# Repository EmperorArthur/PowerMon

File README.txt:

This is the code and Eagle files for a wireless power monitoring system.
All code and schematics are Copyright Arthur Moore 2013 GPLV3
	If this license is too restrictive for your use, feel free to contact me.

The wireless power monitor works using two boards with IEE 802.15.4 Radios.
One board monitors and transmits power usage data, while the other recieves the data, and sends it on to a computer.

Currently there is one board that does everything.  It uses an ATMega328 microcontroller with an AT86RF231 radio module.

This repository was taken from an SVN snapshot, then sanitized for public release.

The code is in ./Code/Datalogger1/

Important files are:
ADC.h/c:				These are the Analog to Digital Converter functions.
LED.h/c:				Simple functions to controll a LED
Communication.h/c:		Bridge functions, allowing cout to work with both serial and the radio.
UART.h/c:				Serial I/O for cout and cin
Measurements.h/c:		Where the actual measurements are done and calculated.
Datalogger1.c:			The main file.  This is where the important stuff takes place.

Contrary to any common sense, the main board is in ./Eagle Files/Main Board with Headers/

The only header on the board is a SPI programming header.
I normally use an arduino bootloader with the FTDI chip, so it's mostly unused.
There is one wire missing for this configuration.  A wire from the FTDI chip to the reset pin with a small capacitor in series.

I was orriginally using an older version of the radio library provided here:  http://simonetti.media.mit.edu/dev/projects/avrradio
Given my issues with the library documentation and microcontroller space issues, I had to hack the provided library to pieces.
I eventually ended up creating my own library from scratch for this thing.  See my github page for it.

To Do:
	Replace hacked together radio library with the one I created.
	Re-organize the repository so It's easy to understand, and doesn't have as many misc files.
	Completely redesign board for smaller footprint, less component count, and higher acuracy.
	Potentially seperate board into two seperate boards.

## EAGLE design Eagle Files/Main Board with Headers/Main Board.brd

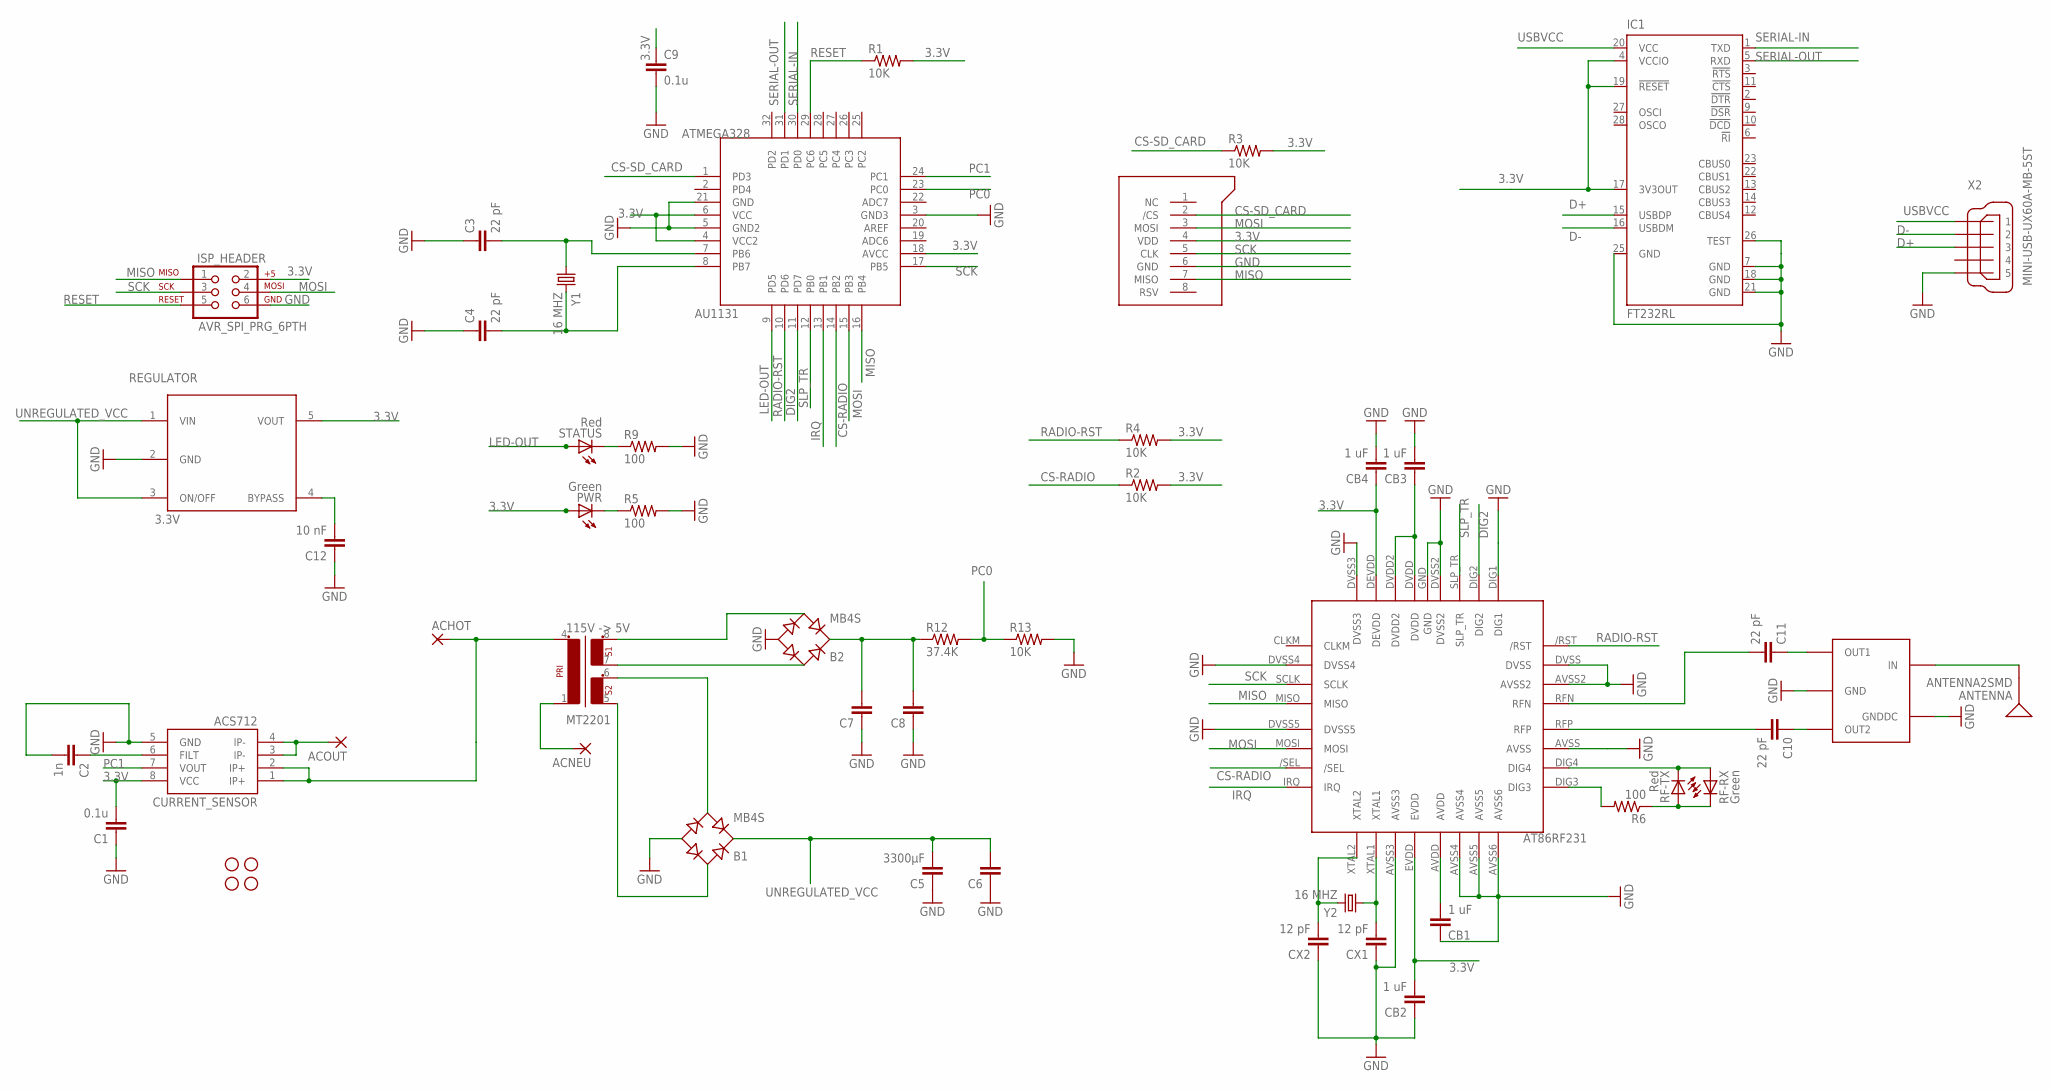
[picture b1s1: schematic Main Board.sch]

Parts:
3.3V_REGULATOR: REG3.3V; SOT23-5
ACHOT: PTH3MM; PTH-3MM
ACNEU: PTH3MM; PTH-3MM
ACOUT: PTH3MM; PTH-3MM
ANTENNA: ANTENNA2SMD; ANTENNA-CHIP2
AT86RF231: AT86RF231(RADIO)AT86RF231; 32QN2(RADIO)
ATMEGA328: ATMEGA32832A; TQFP32-08
B1, B2: MB4S; SOIC-4
BALUN: WE-BAL
C1, C9: 0.1u; 0603-CAP
C2: 1n; 0603-CAP
C3, C4, C10, C11: 22 pF; 0603-CAP
C5: 3300µF; CAP-PTH-5MM
C6, C7, C8: CAPPTH1; CAP-PTH-5MM
C12: 10 nF; 0603-CAP
CB1, CB2, CB3, CB4: 1 uF; 0603-CAP
CURRENT_SENSOR: ACS712; SO08
CX1, CX2: 12 pF; 0603-CAP
IC1: FT232RL; SSOP28
ISP_HEADER: AVR_SPI_PRG_6PTH; 2X3
JP1, JP2, JP3, JP4: STAND-OFF
MICROSD: MICROSD; MICRO-SD-SOCKET-PP
MT2201: 115V -> 5V; EI38-2
PWR: Green; LED-0603
R1, R2, R3, R4, R13: 10K; 0603-RES
R5, R6, R9: 100; 0603-RES
R12: 37.4K; 0603-RES
RF-RX: Green; LED-0603
RF-TX: Red; LED-0603
STATUS: Red; LED-0603
X2: MINI-USB-UX60A-MB-5ST; UX60A-MB-5ST
Y1, Y2: 16 MHZ; HC49UP

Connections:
3.3V: 3.3V_REGULATOR.5 (VOUT), AT86RF231.DEVDD, AT86RF231.EVDD, ATMEGA328.4 (VCC2), ATMEGA328.6 (VCC), ATMEGA328.18 (AVCC), C1.2, C9.1, CB2.2, CB4.1, CURRENT_SENSOR.8 (VCC), IC1.4 (VCCIO), IC1.17 (3V3OUT), IC1.19 (!RESET), ISP_HEADER.2, MICROSD.4 (VDD), PWR.A, R1.2, R2.2, R3.2, R4.2
3.3V1: 3.3V_REGULATOR.4 (BYPASS), C12.2
CS-RADIO: AT86RF231./SEL, ATMEGA328.14 (PB2), R2.1
CS-SD_CARD: ATMEGA328.1 (PD3), MICROSD.2 (/CS), R3.1
D+: IC1.15 (USBDP), X2.3
D-: IC1.16 (USBDM), X2.2
DIG2: AT86RF231.DIG2, ATMEGA328.11 (PD7)
GND: 3.3V_REGULATOR.2 (GND), AT86RF231.AVSS, AT86RF231.AVSS2, AT86RF231.AVSS3, AT86RF231.AVSS4, AT86RF231.AVSS5, AT86RF231.AVSS6, AT86RF231.DIG1, AT86RF231.DVSS, AT86RF231.DVSS2, AT86RF231.DVSS3, AT86RF231.DVSS4, AT86RF231.DVSS5, AT86RF231.GND, ATMEGA328.3 (GND3), ATMEGA328.5 (GND2), ATMEGA328.21 (GND), B1.-, B2.-, BALUN.GND, BALUN.GNDDC, C1.1, C2.2, C3.1, C4.1, C5.1, C6.1, C7.1, C8.1, C9.2, C12.1, CB1.1, CB2.1, CB3.2, CB4.2, CURRENT_SENSOR.5 (GND), CX1.1, CX2.1, IC1.7 (GND), IC1.18 (GND), IC1.21 (GND), IC1.25 (GND), IC1.26 (TEST), ISP_HEADER.6, MICROSD.6 (GND), R5.2, R9.2, R13.2, X2.5
IRQ: AT86RF231.IRQ, ATMEGA328.13 (PB1)
LED-OUT: ATMEGA328.9 (PD5), STATUS.A
MISO: AT86RF231.MISO, ATMEGA328.16 (PB4), ISP_HEADER.1, MICROSD.7 (MISO)
MOSI: AT86RF231.MOSI, ATMEGA328.15 (PB3), ISP_HEADER.4, MICROSD.3 (MOSI)
unnamed: ACHOT.1, CURRENT_SENSOR.1 (IP+), CURRENT_SENSOR.2 (IP+), MT2201.4
unnamed: ACNEU.1, MT2201.1
unnamed: B1.~1 (AC1), MT2201.5
unnamed: B2.~1 (AC1), MT2201.7
unnamed: B2.~2 (AC2), MT2201.8
unnamed: B2.+, C7.2, C8.2, R12.1
unnamed: PWR.C, R5.1
unnamed: AT86RF231.DVDD, AT86RF231.DVDD2, CB3.1
unnamed: ACOUT.1, CURRENT_SENSOR.3 (IP-), CURRENT_SENSOR.4 (IP-)
unnamed: AT86RF231.AVDD, CB1.2
unnamed: AT86RF231.XTAL1, CX1.2, Y2.1
unnamed: AT86RF231.XTAL2, CX2.2, Y2.2
unnamed: AT86RF231.DIG4, RF-RX.A, RF-TX.C
unnamed: R6.1, RF-RX.C, RF-TX.A
unnamed: AT86RF231.DIG3, R6.2
unnamed: BALUN.OUT2, C10.1
unnamed: BALUN.OUT1, C11.1
unnamed: AT86RF231.RFN, C11.2
unnamed: AT86RF231.RFP, C10.2
unnamed: ANTENNA.FEED, BALUN.IN
unnamed: B1.~2 (AC2), MT2201.6
unnamed: C2.1, CURRENT_SENSOR.6 (FILT)
unnamed: R9.1, STATUS.C
PC0: ATMEGA328.23 (PC0), R12.2, R13.1
PC1: ATMEGA328.24 (PC1), CURRENT_SENSOR.7 (VOUT)
RADIO-RST: AT86RF231./RST, ATMEGA328.10 (PD6), R4.1
RESET: ATMEGA328.29 (PC6), ISP_HEADER.5, R1.1
SCK: AT86RF231.SCLK, ATMEGA328.17 (PB5), ISP_HEADER.3, MICROSD.5 (CLK)
SERIAL-IN: ATMEGA328.30 (PD0), IC1.1 (TXD)
SERIAL-OUT: ATMEGA328.31 (PD1), IC1.5 (RXD)
SLP_TR: AT86RF231.SLP_TR, ATMEGA328.12 (PB0)
UNREGULATED_VCC: 3.3V_REGULATOR.1 (VIN), 3.3V_REGULATOR.3 (ON/OFF), B1.+, C5.2, C6.2
USBVCC: IC1.20 (VCC), X2.1
XTAL1: ATMEGA328.7 (PB6), C3.2, Y1.1
XTAL2: ATMEGA328.8 (PB7), C4.2, Y1.2

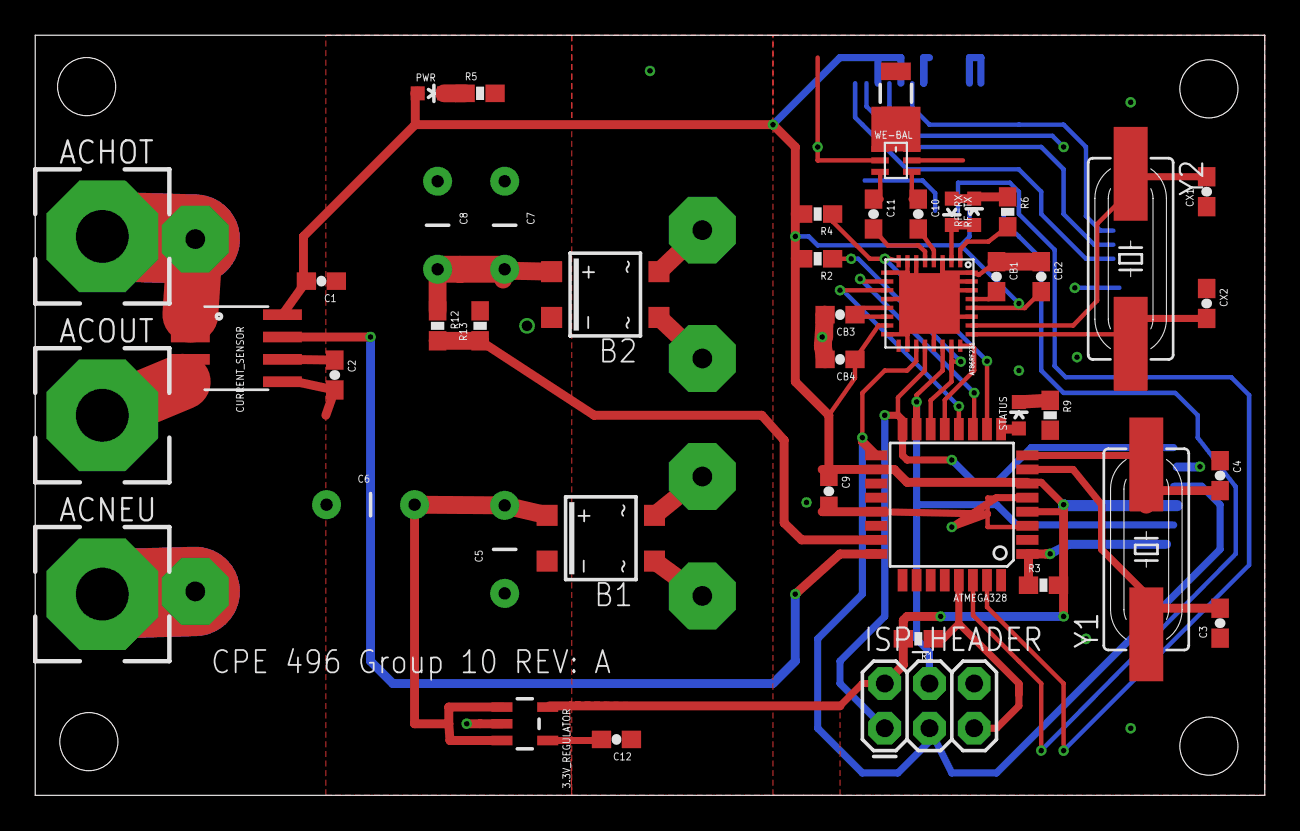
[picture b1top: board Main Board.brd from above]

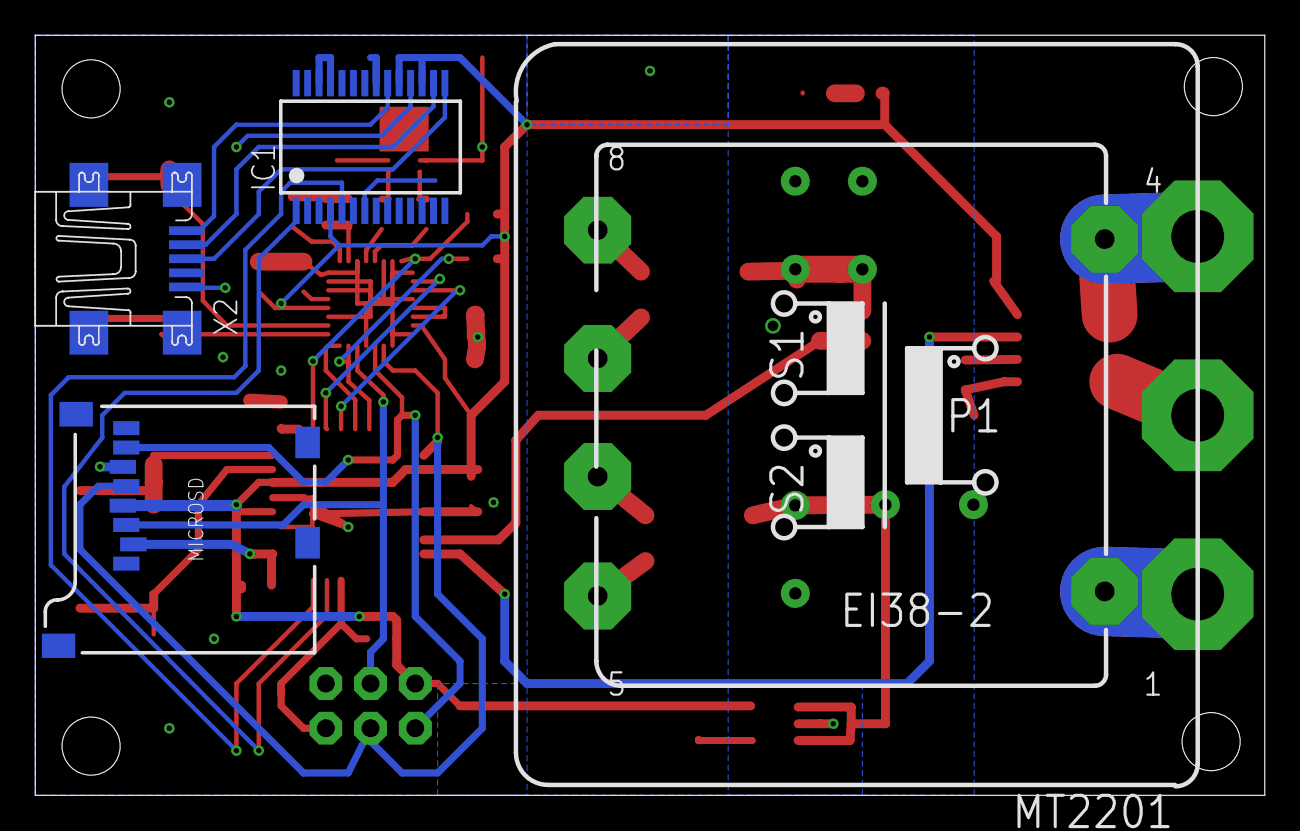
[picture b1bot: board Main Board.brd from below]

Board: 2 copper layers, 69.8 x 43.2 mm, 53 parts (4 on the bottom side), 47 nets.

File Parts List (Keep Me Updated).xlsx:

Qty | Value | Device | Parts | Price Per Part | Price Per Board | For 3 Boards | Part Order Page | Part Description | Already have | Minimum Order
1 | ACS712 | ACS712 | CURRENT_SENSOR | 4.5199999999999996 | 4.5199999999999996 | 13.559999999999999 | http://parts.digikey.com/1/parts/945626-sensor-current-20a-5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 | current-sensor | yes | 3
1 | ANTENNA2SMD | ANTENNA2SMD | ANTENNA | 0.84399999999999997 | 0.84399999999999997 | 2.532 | http://search.digikey.com/us/en/products/2450AT18B100E/712-1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 | RF antenna | no | Order at least 10
1 | AT86RF231(RADIO)AT86RF231 | AT86RF231(RADIO)AT86RF231 | AT86RF231 | 4.7300000000000004 | 4.7300000000000004 | 14.190000000000001 | http://search.digikey.com/us/en/products/AT86RF231-ZU/AT86RF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 | radio | no | 3
1 | ATMEGA32832A | ATMEGA32832A | ATMEGA328 | 3.83 | 3.83 | 11.49 | http://parts.digikey.com/1/parts/1877362-ic-mcu-avr-32k-flas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 | atmega | yes | 3
1 | AVR_SPI_PRG_6PTH | AVR_SPI_PRG_6PTH | ISP_HEADER | 0.39 | 0.78 | 2.34 | http://search.digikey.com/us/en/products/961206-6404-AR/3M94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 | ISP header | no | Order at least 10
2 | 0.1u | CAP0603-CAP | C1, C9 | 1.2500000000000001E-2 | 0.05 | 1.25 | http://search.digikey.com/us/en/products/CC0603ZRY5V9BB104/3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 | 0.1uF Cap | no | Order at least 100
4 | 1 uF | CAP0603-CAP | CB1, CB2, CB3, CB4 | 3.0599999999999999E-2 | 3.0599999999999999E-2 | 3.06 | http://search.digikey.com/us/en/products/C1608Y5V1A105Z/445-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 | 1 uF Caps | no | Order at least 100
1 | 1n | CAP0603-CAP | C2 | 1.5299999999999999E-2 | 1.5299999999999999E-2 | 1.53 | http://search.digikey.com/us/en/products/GRM188R71H102KA01D/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 | 1nF Cap | no | Order at least 100
1 | 10 nF | CAP0603-CAP | C12 | 1.4E-2 | 2.8000000000000001E-2 | 1.4 | http://search.digikey.com/us/en/products/GRM188R71H103KA01D/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 | 10nF Cap | no | Order at least 100
2 | 12 pF | CAP0603-CAP | CX1, CX2 | 2.2499999999999999E-2 | 0.09 | 2.25 | http://search.digikey.com/us/en/products/C1608C0G1H120J/445-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 | 12pF Caps | no | Order at least 100
4 | 22 pF | CAP0603-CAP | C3, C4, C10, C11 | 2.2499999999999999E-2 | 6.7500000000000004E-2 | 2.25 | http://search.digikey.com/us/en/products/C1608C0G1H220J/445-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 | 22pF Caps | no | Order at least 100
3 |  | CAPPTH1 | C6, C7, C8 | - | - | - | - | Ignore these
1 | 3300µF | CAPPTH1 | C5 | 0.9 | 1.8 | 5.4 | http://search.digikey.com/us/en/products/ECA-1CM332/P5144-ND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 | 3300uF Cap | no | 6
2 | 16 MHZ | CRYSTALSMD | Y1, Y2 | 0.35799999999999998 | 0.35799999999999998 | 3.58 | http://parts.digikey.com/1/parts/1800664-crystal-16-000-mhz-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 | 16mhz crystal | yes | Order at least 10
1 | 115V -> 5V | EI38-2 | MT2201 | 4.28 | 4.28 | 12.84 | http://search.digikey.com/us/en/products/3FS-210/MT2201-ND/285599 | transformer | no | 3
1 | FT232RL | FT232RL | IC1 | 4.5 | 9 | 27 | http://parts.digikey.com/1/parts/1501976-ic-usb-fs-serial-ua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 | USB-Serial Chip | no | 6
2 | Green | LED0603 | PWR, RF-RX | 0.11700000000000001 | 0.23400000000000001 | 1.17 | http://search.digikey.com/us/en/products/APT1608SGC/754-1121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 | green led | no | Order at least 10
2 | Red | LED0603 | RF-TX, STATUS | 0.11700000000000001 | 0.23400000000000001 | 1.17 | http://search.digikey.com/us/en/products/APT1608EC/754-1117-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 | red led | no | Order at least 10
2 | MB4S | MB4S | B1, B2 | 0.41399999999999998 | 0.41399999999999998 | 4.1399999999999997 | http://parts.digikey.com/1/parts/1422327-ic-rect-bridge-0-5a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 | bridge rectifier | no | Order at least 10
1 | MICROSD | MICROSD | MICROSD | 1.94 | 1.94 | 5.82 | http://parts.digikey.com/1/parts/1804297-conn-mini-micro-sd-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 | microsd | yes | 3
1 | MINI-USB-UX60A-MB-5ST | MINI-USB-UX60A-MB-5ST | X2 | 1.0229999999999999 | 3.069 | 10.23 | http://search.digikey.com/us/en/products/UX60A-MB-5ST/H2961C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 | mini USB | no | Order at least 10
3 |  | PTH3MM | ACHOT, ACNEU, ACOUT | - | - | - | - | Ignore these
1 | REG3.3V | REG3.3V | 3.3V_REGULATOR | 0.66 | 0.66 | 1.98 | http://parts.digikey.com/1/parts/609150-ic-ldo-reg-3-3v-150m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 | 3.3v regulator | yes | 3
5 | 10K | RESISTOR0603-RES | R1, R2, R3, R4, R13 | 1.5800000000000002E-2 | 7.9000000000000015E-2 | 1.58 | http://search.digikey.com/us/en/products/RNCP0603FTD10K0/RNC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 | 10k resistor | no | Order at least 100
1 | 37.4K | RESISTOR0603-RES | R12 | 1.5800000000000002E-2 | 1.5800000000000002E-2 | 1.58 | http://search.digikey.com/us/en/products/RNCP0603FTD37K4/RNC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 | 37.4K resistor | no | Order at least 100
3 | 100 | RESISTOR0603-RES | R5, R6, R9 | 1.5800000000000002E-2 | 4.7400000000000005E-2 | 1.58 | http://search.digikey.com/us/en/products/RNCP0603FTD100R/RNC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 | 100 ohm resistor | no | Order at least 100
4 | STAND-OFF | STAND-OFF | JP1, JP2, JP3, JP4 | - | - | - | - | Ignore these
1 | WE-BAL | WE-BAL | BALUN | 2.58 | 2.58 | 7.74 | http://parts.digikey.com/1/parts/1790682-balun-ember351-357-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 | balun | no | 3
1 |  |  | To Outlet | 0.79700000000000004 | 0.79700000000000004 | 7.97 | http://search.digikey.com/us/en/products/703W-00%2F07/Q335-N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 | Euro IN |  | Order at least 10
1 |  |  | To Device | 1.1299999999999999 | 1.1299999999999999 | 3.3899999999999997 | http://search.digikey.com/us/en/products/Q-712/Q527-ND/2180784 | Edison Out |  | 3
 |  |  | Wire
1 |  |  | Case | 3 | 3 | 9 | http://search.digikey.com/us/en/products/CU-1874-B/377-1165-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 | Enclosure |  | 3
 |  |  | Board Cost
 |  |  |  |  | 41.62360000000001 | 153.02200000000005 | Total
 |  |  |  |  |  | -28.151200000000017 | Cost overhead from spare/unused parts

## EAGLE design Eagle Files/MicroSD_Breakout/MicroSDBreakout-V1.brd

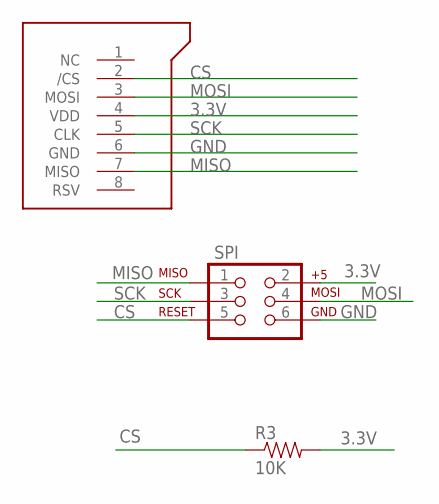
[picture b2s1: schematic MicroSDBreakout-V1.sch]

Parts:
R3: 10K; 0603-RES
SPI: AVR_SPI_PRG_6PTH; 2X3
U$1: MICROSD; MICRO-SD-SOCKET-PP

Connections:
3.3V: R3.2, SPI.2, U$1.4 (VDD)
CS: R3.1, SPI.5, U$1.2 (/CS)
GND: SPI.6, U$1.6 (GND)
MISO: SPI.1, U$1.7 (MISO)
MOSI: SPI.4, U$1.3 (MOSI)
SCK: SPI.3, U$1.5 (CLK)

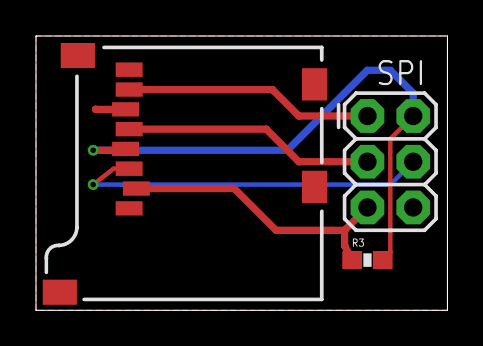
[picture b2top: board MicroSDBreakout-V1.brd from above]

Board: 2 copper layers, 22.9 x 15.2 mm, 3 parts (0 on the bottom side), 6 nets.

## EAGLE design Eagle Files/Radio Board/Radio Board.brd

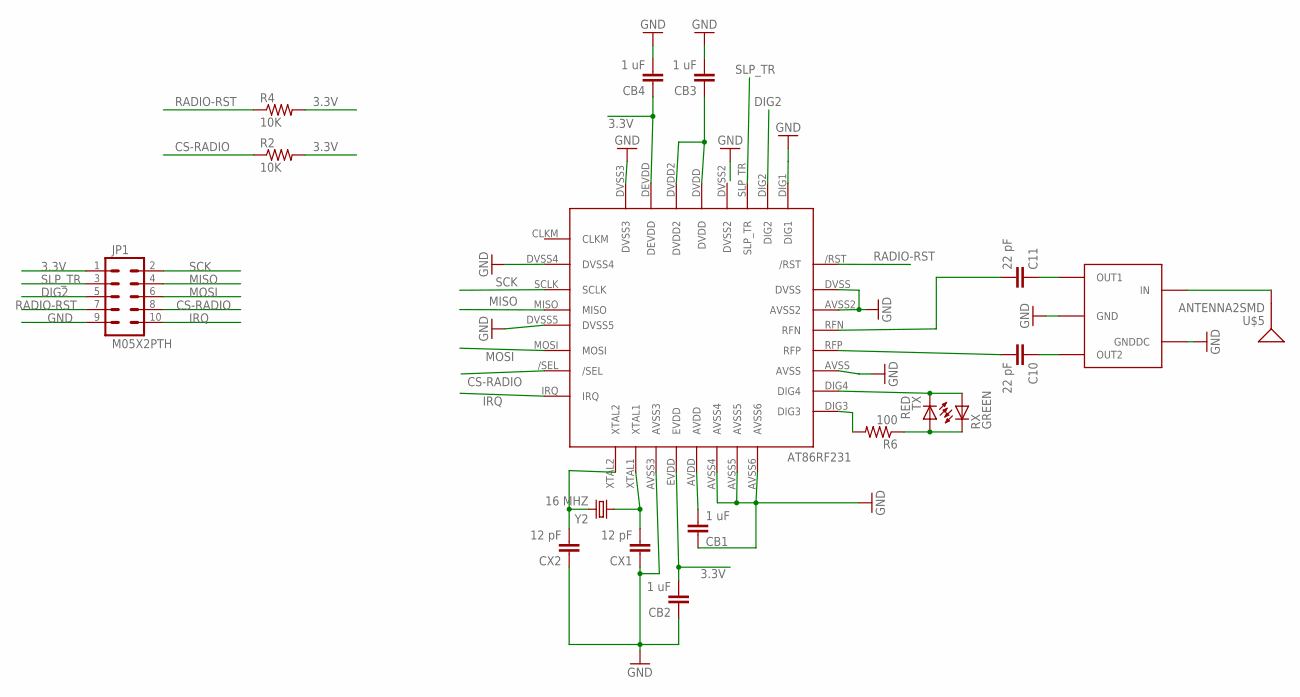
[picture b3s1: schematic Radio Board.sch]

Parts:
C10, C11: 22 pF; 0603-CAP
CB1, CB2, CB3, CB4: 1 uF; 0603-CAP
CX1, CX2: 12 pF; 0603-CAP
JP1: M05X2PTH; AVR_ICSP
R2, R4: 10K; 0603-RES
R6: 100; 0603-RES
RX: GREEN; LED-0603
TX: RED; LED-0603
U$3: AT86RF231(RADIO)AT86RF231; 32QN2(RADIO)
U$4: WE-BAL
U$5: ANTENNA2SMD; ANTENNA-CHIP2
Y2: 16 MHZ; HC49UP

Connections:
3.3V: CB2.2, CB4.1, JP1.1, R2.2, R4.2, U$3.DEVDD, U$3.EVDD
CS-RADIO: JP1.8, R2.1, U$3./SEL
DIG2: JP1.5, U$3.DIG2
GND: CB1.1, CB2.1, CB3.2, CB4.2, CX1.1, CX2.1, JP1.9, U$3.AVSS, U$3.AVSS2, U$3.AVSS3, U$3.AVSS4, U$3.AVSS5, U$3.AVSS6, U$3.DIG1, U$3.DVSS, U$3.DVSS3, U$3.DVSS4, U$3.DVSS5, U$4.GND, U$4.GNDDC
IRQ: JP1.10, U$3.IRQ
MISO: JP1.4, U$3.MISO
MOSI: JP1.6, U$3.MOSI
unnamed: CB3.1, U$3.DVDD, U$3.DVDD2
unnamed: CB1.2, U$3.AVDD
unnamed: CX1.2, U$3.XTAL1, Y2.1
unnamed: CX2.2, U$3.XTAL2, Y2.2
unnamed: RX.A, TX.C, U$3.DIG4
unnamed: R6.1, RX.C, TX.A
unnamed: R6.2, U$3.DIG3
unnamed: C10.1, U$4.OUT2
unnamed: C11.1, U$4.OUT1
unnamed: C11.2, U$3.RFN
unnamed: C10.2, U$3.RFP
unnamed: U$4.IN, U$5.FEED
RADIO-RST: JP1.7, R4.1, U$3./RST
SCK: JP1.2, U$3.SCLK
SLP_TR: JP1.3, U$3.SLP_TR

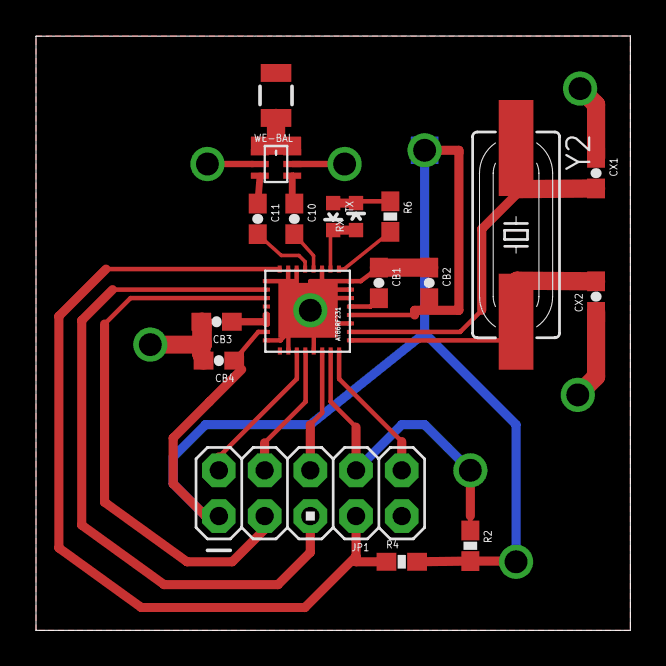
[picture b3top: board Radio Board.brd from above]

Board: 2 copper layers, 33.0 x 33.0 mm, 18 parts (0 on the bottom side), 22 nets.

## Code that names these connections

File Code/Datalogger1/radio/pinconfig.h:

#define SLP_TR ( PB0 )
#define DDR_SLP_TR ( DDRB )
#define PORT_SLP_TR ( PORTB )
#define PIN_SLP_TR ( PINB )
#define RST ( PD6 )
#define DDR_RST ( DDRD )
#define PORT_RST ( PORTD )
#define PIN_RST ( PIND )
#define HAL_PORT_SPI ( PORTB )
#define HAL_DDR_SPI ( DDRB )
#define HAL_SS_PIN ( PB2 )
#define HAL_DD_SS ( PB2 )
#define HAL_DD_SCK ( PB5 )
#define HAL_DD_MOSI ( PB3 )
#define HAL_DD_MISO ( PB4 )
#define RADIO_LED_ACTIVE_LOW ( 0 )
#define RADIO_LED_HAVE_DUAL ( 0 )
#define RADIO_LED1 ( PD5 )
#define RADIO_LED1_DDR ( DDRD )
#define RADIO_LED1_PORT ( PORTD )
#define RADIO_LED2 ( PD5 )
#define RADIO_LED2_DDR ( DDRD )
#define RADIO_LED2_PORT ( PORTD )
#define HAL_TCCRB ( TCCR1B )
#define HAL_TCNT ( TCNT1 )
#define HAL_TIMSK ( TIMSK1 )
#define HAL_TIFR ( TIFR1 )
#define HAL_TRX_ISR ( TIMER1_CAPT_vect )
#define HAL_OVF_ISR ( TIMER1_OVF_vect )

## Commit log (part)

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2012-02-25 Added folders that subversion normally uses for dealing with branches and tags.
    --Arthur
2012-02-25 Moved all the files into trunk where they belong.
    Here is how you get your local copy to look the same as before:
    1. Right click the folder that had everything in it.
    2. Select the TortoiseSVN drop down menu
    3. Click the "Relocate" option.
    4. Put "https://cd-net.net/CPE496/trunk" in the dialog box.
    5. Click "OK"
2012-02-26 There was a major flaw with the radio package. Corrected it.
    The radio package accidentally had the tPlace and tName layers on the Top layer.
    --Arthur
2012-02-26 Fixed a few things in the Main Board.
    I updated the main board to use the new Radio part.
    I also changed the ground plane distance to 20 mil.
    --Arthur
2012-02-26 The Radio Board is now ready to be used with a 10 pin header.
    --Arthur
2012-02-26 The MicroSD Breakout board is now ready to be used with a 10 pin header.
    --Arthur
2012-02-26 MicroSD Breakout Board now has a pull up resistor on CS
    --Arthur
2012-02-26 Radio Board now has pull up resistors on Radio Reset, and Radio CS.
    --Arthur
2012-03-02 Removed Files for Printing
    Files for Printing are something I'm using locally.
    There is no need for them to be in the repository.
    --Arthur
2012-03-02 Updated Boards
    --Arthur
2012-03-02 Added a main board that uses separate boards for everything.
    --Arthur
2012-03-05 More updates to the Main Board with Headers.
    The transformer will now be under the board, so now we can place things inside that footprint on the top.
    This saves us something around a square inch or two of board space.
    --Arthur
2012-03-06 Latest Update to all the boards.
    --Arthur
2012-03-20 Added Arduino Code to test the SD Card
    --Arthur
2012-03-20 Added a simple Arduino script to test whether the prototype board is working or not.
    Blinks the LED
    --Arthur
2012-03-20 Added code for use with WinAVR and avrdude.
    This is one way of programing the prototype board.
    --Arthur
2012-03-20 Added Datasheet for Capacitors
    --Arthur
2012-03-20 Updated "Main Board with Headers" so the ground plane is safely away from AC power.
    --Arthur
2012-03-20 Added a picture that maps from Arduino pins to our ATMega pins.
    --Arthur
2012-03-22 Updated the list of commands to program our board.
    --Arthur
2012-03-22 Updated Datalogger code.
    --Arthur
2012-03-22 Updated avrdude command to exactly what I'm using.
    --Arthur
2012-03-22 Updated my Datalogger code
    Put the Power Measurement stuff in a separate file that we currently aren't using.
    Cut down on the number of Arduino Functions we're using.
    Using these Arduino Functions:
    3 x pinMode(...) to set the output pins.
    2 x Delay(...) for my LED Blink function.
    Serial.* for debugging (Currently disabled by a #define)
2012-03-22 Datalogger now can use the ADC interrupt.
    I had forgotten about the 'volatile' keyword
    --Arthur
2012-03-22 Re-Added Sparkfun ATMega package.
    The Sparkfun package for our ATMega was removed form the library when Joel updated the transformer, I've re-added it.
    --Arthur
2012-03-23 Headers board now has the SD Card holder integrated into it.
    This saves us board space, and brings us one step closer to a nice integrated board.
    --Arthur
2012-03-23 Cleaned up the Board some in preparation for integration.
    TODO:
    Fix the Radio Part in the library to reflect the ground plane on the device.
    Consider putting either the balun and antenna or the crystal oscilator on the bottom of the board.
    --Arthur
2012-03-24 Code Update
    I've included everything I use to program my board except the Arduino compiler.
    It's looking like averaging is working instead of RMS for some unknown reason right now, but I need to get a variable voltage source/current sync and check this.
    In other news the transformer seems to be putting out more voltage than it should. It's supposed to be a 23:1 Ratio, but I was measuring 6.4V on the secondaries and my Kill-A-Watt was saying 123V on 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
    TODO:
    Get a variable voltage source/current sync and test the linearity of my measurements.
    If they're linear, then I can account for any weird offsets, ratios.
2012-03-25 Main Board with Headers is now almost ready.
    I'm adding the FTDI Module right now.
    TODO:
    1. Double check regulator Datasheet. I think we're missing a capacitor.
    2. Update Radio Module Schematics to incorporate ground plane.
    3. Check if the hall effect sensor can work linearly at 3.3V
    4. Finish Adding FTDI chip and USB connector.
2012-03-25 Ground plane for the radio module inserted.
2012-03-25 Added data sheets for the FTDI chip and the USB connector.
    --Arthur
2012-03-25 Added USB to Serial Capability to the board.
    --Arthur
2012-03-25 Library update.
    Radio Board package now has a ground plane.
    The tPlace layer now correctly outlines the chip
    TODO:
    Mark Pin 1 on the tPlace layer.
    Adjust the symbol so that all the pins are grid aligned.
    Make sure that the pin spacing is correct.
2012-03-27 Updated Parts List
    --Arthur
2012-03-28 Added more data sheets.
    Added:
    A data sheet that has the recommended layout for QFN 32 pin size/spacing.
    A data sheet for the Female Edison connector we're using.
    A data sheet for the Euro connector we're using.
    --Arthur
2012-03-28 Updated Parts List --Arthur
2012-03-28 Updated the Board we're having made.
    --Arthur
2012-03-28 Updated Library.
    This is the Library used for the Rev A board.
    --Arthur
2012-03-28 Modified Price List
    This is the final price list for everything we need to make 3 boards.
    It does not include the cost of 10AWG wire. (DigiKey wants us to buy to much)
    Also included is a rubric for delivery time vs number of boards.
    This will let us choose the best option for PCB manufacturing.
    --Arthur
2012-04-24 Updated Parts List in Trunk to represent what we really ordered for Rev A.
    --Arthur
2012-04-27 Broken my main Datalogger1 file into some nice sub files.
    --Arthur
2012-04-27 Renamed Power-Measurement.c/h to measurement.c/h
    --Arthur
2012-04-27 Code cleanup for datalogger
    --Arthur
2012-04-27 Revamped Datalogger1
    It now prints to the serial port.
    The SD card is currently non-functional.
    Datalogger1 no longer relies on Arduino libraries.
    --Arthur
2012-04-27 Updated Datalogger1
    --Arthur
2012-04-27 Removed some extranious junk from some of dataloggers files.
    --Arthur
2012-04-28 Updated Datalogger1.c
    --Arthur
2012-04-28 Removed SD Functionality.
    It was being annoying.
    --Arthur
2012-04-28 printLongInt now handles negative numbers.
    --Arthur
2012-04-29 Datalogger now correctly samples at the frequency I define.
    --Arthur
2012-04-29 Datalogger now samples at the maximum possible rate.
    --Arthur
2012-04-29 I had forgotten one last line that referenced time. Fixed.
    --Arthur
2012-05-01 Datalogger1 is done.
    All that's left is code cleanup and Calibration
    --Arthur
2012-05-02 Initial Calibration Completed.
    Now all that's left is code cleanup.
    --Arthur
2012-05-03 Code Cleanup.
    Everything is ready to be printed.
    --Arthur
2012-05-03 Added all of our testing to the repository.
    --Arthur
2012-05-03 Minor Reorganization - Final
    --Arthur
2012-10-08 This is the last commit of Datalogger1.c for Senior Design.
    Everything after this is done on my own time.
2012-10-09 Updated Radio Debugging.
    Now if the radio does not initialize,
    control is returned to main instead of locking forever.
    Main then spits out a warning to the serial port.
    Recursion: The LED no longer works correctly.
2012-10-09 Makefile now can set the EEPROM.
    The avr occasionally loses it's EEPROM, causing the radio to fail.
    This is now the easies way to fix it.
    WARNING: This functionality points to a script outside the build directory.
2012-10-09 Capitalized a few variables which are #defined.
    Code manageability update.
2012-10-09 Stringifying my #defines
    This lets me use sprint instead of printf in more places.
    That saves ram.
2012-10-09 Use stdlib to replace some of my (bad) functions.
    Unfortunately printf in avr-gcc does not work with floating point numbers.
    I hacked a way around it, and was working on several other attempts for a long term fix.
    It turns out that stdlib can convert everything into nice strings for me.
2012-10-09 Replace functions in debug mode as well.
    I was using my hacked together functions in debug mode.
    Now using stdlib
2012-10-09 adc speedup
    The adc takes much longer to preform a conversion if ADMUX has been altered.
    Added checks to make sure ADMUX really needs to be changed.
2012-10-09 Tweaked measurments
    RMS did nothing, so it's now defuncts and non-functional.
    Tweaked the real world calculations so they better match reality.
2012-10-15 Ignore binary files
2012-10-15 Factor out retrieving the ADC result.
2012-10-15 Now compiling with gnu99 flag set.
2012-10-15 Break the calculations done while waiting for the ADC into a separate function.
    This removed quite a bit of old code, while simultaneously cleaning things up.
2012-10-15 Moved ADC globals to the .c file.
    I don't like these, but they're currently necessary.
2012-10-15 Moved some radio globals into the .c file
    Some of these aren't even needed.
2012-10-15 Fixed a return type error.
    The returned value is unused, but it fixed an error message while I'm playing with c++.
2012-10-15 Don't rely on any ADC global values.
    I forgot to commit this when I removed the ADC globals.
2012-10-15 Switch from C to C++
    The compiler complains more, but I now have much more power.
2012-10-15 The ADC can now execute a function before returning the new value.
    This is done by passing the function and arguments to a special adc function.
    This adds pointer complexity, but avoids the need for and ADC interrupt.
    Measurements now ueses this.
2012-10-15 Moved all my communication stuff to a separate file.
    WARNING: I can't get rid of the radio_transmit() function until I fix the reciever.
    Right now the receiver auto adds newlines to every received message.
2012-10-15 Make Timer1 Interrupt blocking.
    The only reason it was non-blocking was the ADC.
    Once that was fixed it was just a liability.
2012-10-15 Split the main output into a separate function.
    As a reminder, I shouldn't be using the two globals.
2012-10-15 Got rid of an unneeded loop.
    Everything now happens in the timer interrupt, or setup().
2012-10-15 Changed the makefile so communication.c is actually compiled.
2012-10-15 Changed all my guards from measurement.c to Datalogger.c
    This allows me to more easily see what the maximum frequency of the device is.
2012-10-15 Fix an off by one error in the calculations.
    The number of samples was one too high.
    Since it was one out of 1500 it isn't really noticeable.
2012-10-15 Make more emergency cases atomic.
2012-10-17 Moved the LED stuff to a different file.
    Also fixed a bug in the LED code that was preventing it from working.
2013-03-10 Added a File which details the Pinout from the Microcontroller.
2013-03-16 Preparing to publish repository.
    Added Readme and License Files
2013-03-17 Replaced hacked together radio library with a git submodule.
    To use, execute: "git submodule init;git submodule update"
    I was forced to hack the original radio library to pieces, so I eventually just wrote my own.
2013-03-17 Removed duplicate files.
    My radio library already has these, so I'm getting rid of them.
2013-03-17 Fixed a formatting issue with the output.
    dtostrf gives spaces instead of 0s.
    I re-added a function to fix that problem.
2013-03-17 Data is now written to an internal buffer before being output.
    The radio takes a string as its input, so I'm using strcat and an output string as a buffer.

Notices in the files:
parts and their libraries:
SparkFun: Licensing: CC v3.0 Share-Alike You are welcome to use this library for commercial purposes.
